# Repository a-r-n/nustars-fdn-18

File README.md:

# NUSTARS Foundation 2018/19
For remote telemetry and data processing.

## Avionics
Language(s): C++  
Board: Feather M0  
Sensors:  
- BNO055  
- BMP280  
- Adafruit Ultimate GPS  
- ADXL377
Radio: LoRa RFM95W @915MHz
Commercial Altimeters: Raven 4

An ADS is controlled by interpreting signals from the commercial altimeters. General telemetry information is read from custom avionics suite, and is packaged and sent to ground station (as well as being saved to flash). At some point TBD, data will be retransmitted from flash (in the likely event of loss during the flight).

## Ground display and processing
Language(s): Python  
Radio: Feather M0 w/ LoRa RFM95W

The ground station is responsible for interpreting and displaying both real-time and asynchronous data from the avionics package.
Further information TBD

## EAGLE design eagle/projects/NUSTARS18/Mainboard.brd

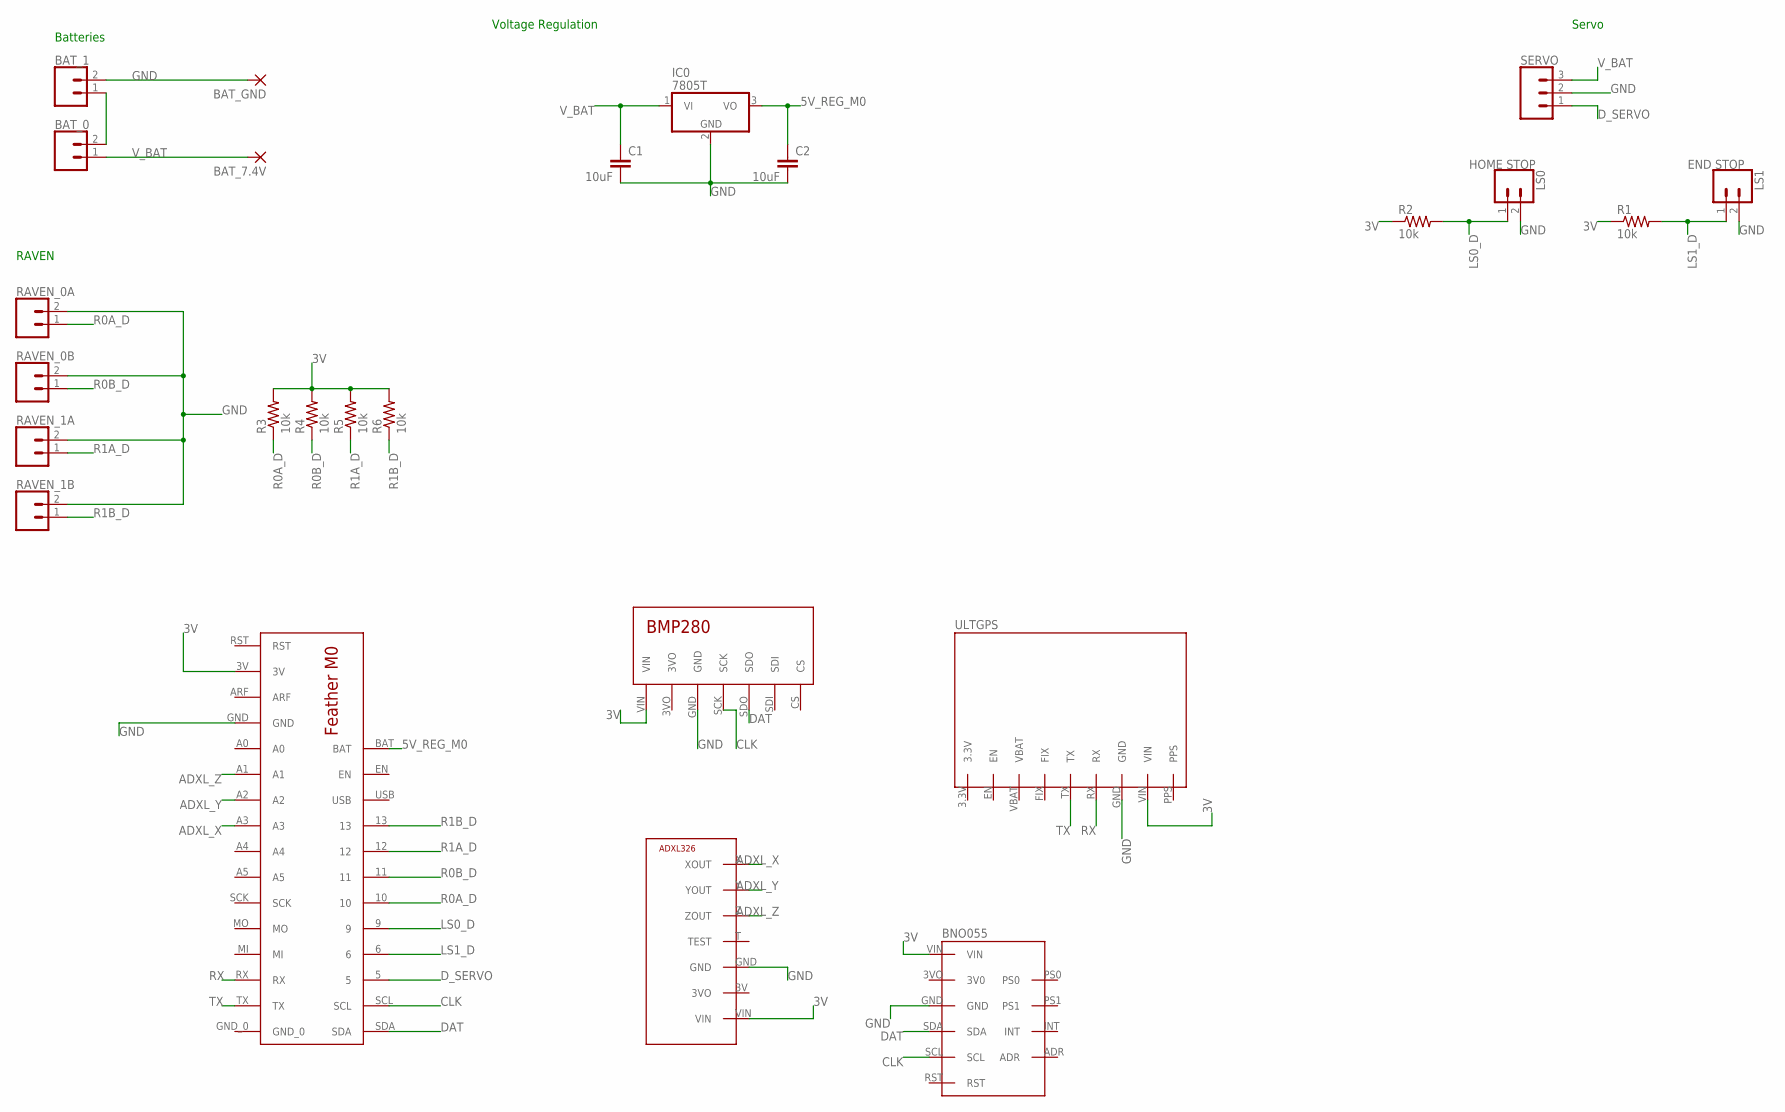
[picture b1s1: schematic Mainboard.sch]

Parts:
BAT_0, BAT_1: CONN_02JST-PTH-2; JST-2-PTH
BAT_7.4V: 3,81/1,4
BAT_GND: 3,81/1,4
C1, C2: 10uF; C2.5-3
IC0: 7805T; TO220H
LS0: HOME STOP; JST-2-PTH
LS1: END STOP; JST-2-PTH
R1, R2, R3, R4, R5, R6: 10k; 0207/10
RAVEN_0A, RAVEN_0B, RAVEN_1A, RAVEN_1B: CONN_02JST-PTH-2; JST-2-PTH
SERVO: CONN_03JST-PTH; JST-3-PTH
U$1: M0
U$2: BMP
U$3: ADXL377
U$4: ULTGPS
U$5: BNO055

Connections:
3V: R1.1, R2.1, R3.2, R4.2, R5.2, R6.2, U$1.3V, U$2.VIN, U$3.VIN, U$4.VIN, U$5.VIN
5V_REG_M0: C2.1, IC0.3 (VO), U$1.BAT
ADXL_X: U$1.A3, U$3.X (XOUT)
ADXL_Y: U$1.A2, U$3.Y (YOUT)
ADXL_Z: U$1.A1, U$3.Z (ZOUT)
B_INT: BAT_0.2, BAT_1.1
CLK: U$1.SCL, U$2.SCK, U$5.SCL
DAT: U$1.SDA, U$2.SDO, U$5.SDA
D_SERVO: SERVO.1, U$1.5
GND: BAT_1.2, BAT_GND.1, C1.2, C2.2, IC0.2 (GND), LS0.2, LS1.2, RAVEN_0A.2, RAVEN_0B.2, RAVEN_1A.2, RAVEN_1B.2, SERVO.2, U$1.GND, U$2.GND, U$3.GND, U$4.GND, U$5.GND
LS0_D: LS0.1, R2.2, U$1.9
LS1_D: LS1.1, R1.2, U$1.6
R0A_D: R3.1, RAVEN_0A.1, U$1.10
R0B_D: R4.1, RAVEN_0B.1, U$1.11
R1A_D: R5.1, RAVEN_1A.1, U$1.12
R1B_D: R6.1, RAVEN_1B.1, U$1.13
RX: U$1.RX, U$4.RX
TX: U$1.TX, U$4.TX
V_BAT: BAT_0.1, BAT_7.4V.1, C1.1, IC0.1 (VI), SERVO.3

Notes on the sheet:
Batteries
Voltage Regulation
Servo
RAVEN

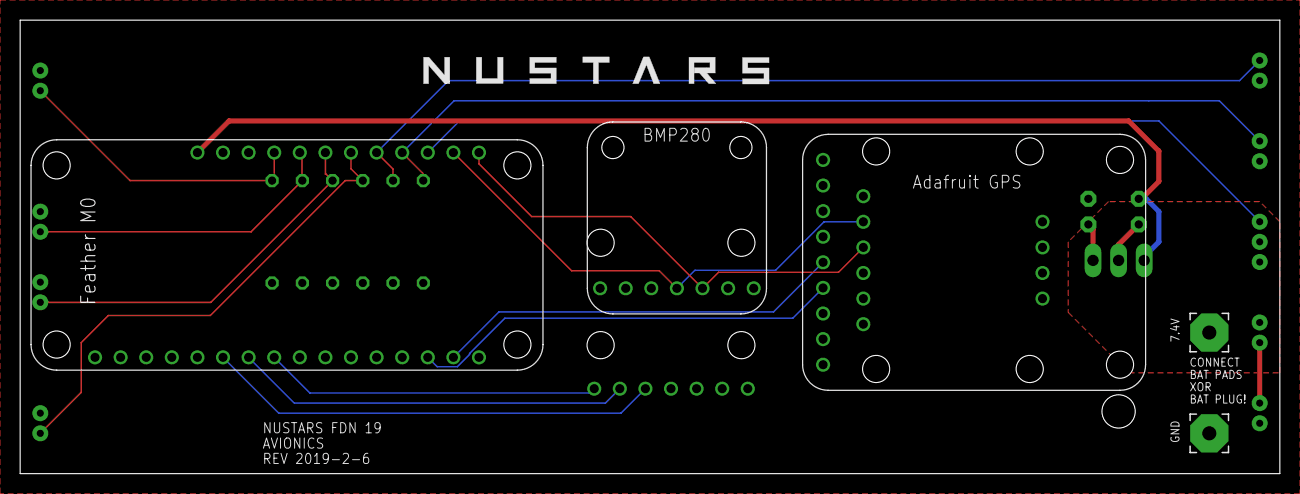
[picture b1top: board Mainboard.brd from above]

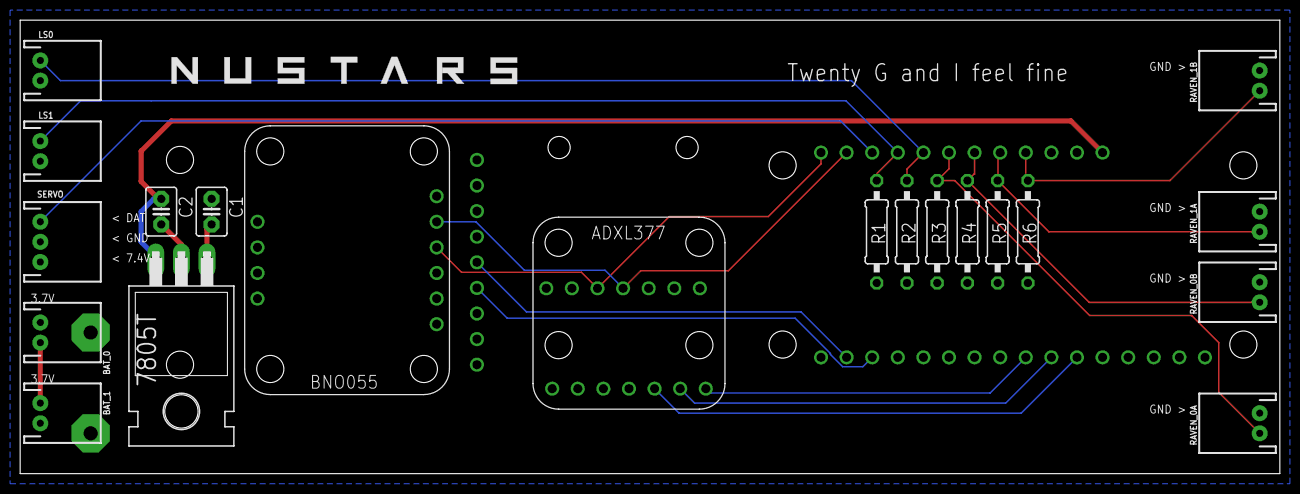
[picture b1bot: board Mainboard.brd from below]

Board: 2 copper layers, 125.0 x 45.0 mm, 25 parts (20 on the bottom side), 19 nets.

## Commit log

2018-10-31 init repo
2018-11-01 Added old libs, modified to allow compilation.
2018-11-01 fixing symlink
2018-11-01 Added external libs
2018-11-01 Added test code for radio throughput
2018-11-02 updated av<->ground code w/ experimental conclusion
2018-11-02 Added ground serial processor for interface with grounduino
2019-01-11 Added EAGLE files
2019-01-16 Updated board to latest requirements
2019-01-16 Updated board according to specs
2019-01-20 Updated the board yet again
2019-02-07 Added Raven JST to board
2019-02-07 Added mass analysis and general board improvements
2019-02-13 Oh boy some ground station programs
    These don't actually do much - but they're a proof of concept
2019-02-24 Updated some radio and other misc code for avionics
2019-02-26 Added data packing and updated radio interface
2019-02-27 Set up servo shell, fixed LEDs
    The LEDs were too bright. Also I made code for l8r
2019-03-06 new ground station
2019-03-07 theoretical launch readiness for test launch
2019-03-10 moved the int to the end
2019-04-23 too much to record honestly, what a good commit note
2019-05-05 added matlab parser et al
2019-05-05 Read from serial
2019-05-07 Add primitive servo code
2019-05-07 added checksum detection to grounduino, fixed BNO init
2019-05-12 we're parsing now
2019-05-12 kalman parser
2019-05-12 kalman
2019-05-14 Revert "Merge branch 'indev' of https://github.com/aaron-r-nelson/nustars-fdn-18 into indev"
    This reverts commit 50abb8c8d71fe784a2d7a3729f3b09f735fa9e54, reversing
    changes made to bd1d956e50ee34f41bb9487fee1f5d352229b994.
2019-05-14 Not destroying files this time
2019-05-14 right spot
2019-05-19 Update parse.m~
2019-05-19 take this
2019-05-19 parse update yayay
2019-05-19 mat:
2019-05-19 plz work
2019-05-19 LESS LIGHT
2019-05-19 parser for the 10000th time
2019-05-19 parser fix
2019-05-19 old parser addition
2019-05-19 matlab
2019-05-19 imperial n stuff
2019-05-19 actual fix merge
2019-05-19 ahhhhhhh
2019-05-19 more imperial
2019-05-19 ahhhh round 2
2019-05-19 Revert "LESS LIGHT"
    This reverts commit cfc7c2c2d01c2e73d02ea08bd9023cd5e27a22e1.
2019-05-19 revert improper commit
2019-05-19 AHHH
2019-06-08 Hopefully the last commit. Good year, all!
2019-06-08 RIP Sky Biscuit

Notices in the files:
parts and their libraries:
SparkFun-Connectors: Licensing: Creative Commons ShareAlike 4.0 International - https://creativecommons.org/licenses/by-sa/4.0
